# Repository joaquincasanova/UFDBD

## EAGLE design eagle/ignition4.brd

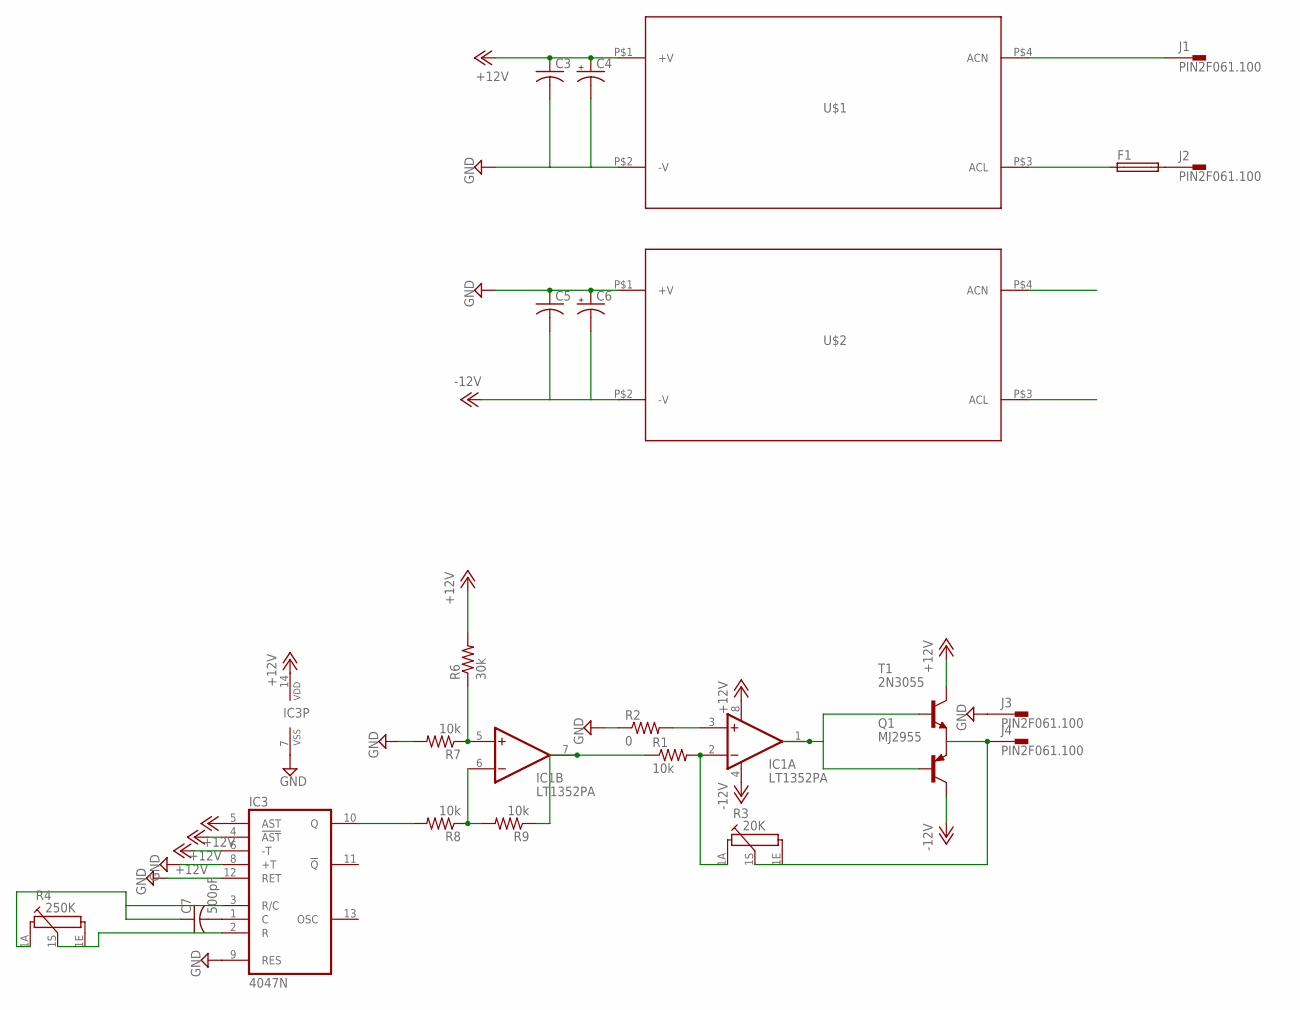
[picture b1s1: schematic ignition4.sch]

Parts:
C3, C5: C-US050-035X075; C050-035X075
C4, C6: CPOL-USE5-5; E5-5
C7: 500pF; C075-042X103
F1: SH25
IC1: LT1352PA; DIL08
IC3: 4047N; DIL14
J1, J2, J3, J4: PIN2F061.100; F061.100
Q1: MJ2955; TO3
R1: 10k; 0207/15
R2: 0; 0207/15
R3: 20K; PC16S
R4: 250K; PC16S
R6: 30k; 0207/12
R7, R8, R9: 10k; 0207/10
T1: 2N3055; TO3
U$1, U$2: IRM-60-12

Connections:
+12V: C3.1, C4.+, IC1.8 (V+), IC3.4 (!AST), IC3.5 (AST), IC3.6 (-T), IC3.14 (VDD), R6.2, T1.C, T1.C/ (C), U$1.P$1 (+V)
-12V: C5.2, C6.-, IC1.4 (V-), Q1.C, Q1.C/ (C), U$2.P$2 (-V)
GND: C3.2, C4.-, C5.1, C6.+, IC3.7 (VSS), IC3.8 (+T), IC3.9 (RES), IC3.12 (RET), J3.A1, J3.A2, R2.1, R7.2, U$1.P$2 (-V), U$2.P$1 (+V)
L: F1.1, U$1.P$3 (ACL), U$2.P$3 (ACL)
N: J1.A1, J1.A2, U$1.P$4 (ACN), U$2.P$4 (ACN)
unnamed: IC1.2 (-IN), R1.2, R3.1A
unnamed: J4.A1, J4.A2, Q1.E, R3.1E, R3.1S, T1.E
unnamed: IC1.7 (OUT), R1.1, R9.1
unnamed: F1.2, J2.A1, J2.A2
unnamed: IC1.1 (OUT), Q1.B, T1.B
unnamed: IC1.3 (+IN), R2.2
unnamed: IC1.5 (+IN), R6.1, R7.1
unnamed: IC1.6 (-IN), R8.1, R9.2
unnamed: IC3.10 (Q), R8.2
unnamed: C7.2, IC3.1 (C)
unnamed: IC3.2 (R), R4.1E, R4.1S
unnamed: C7.1, IC3.3 (R/C), R4.1A

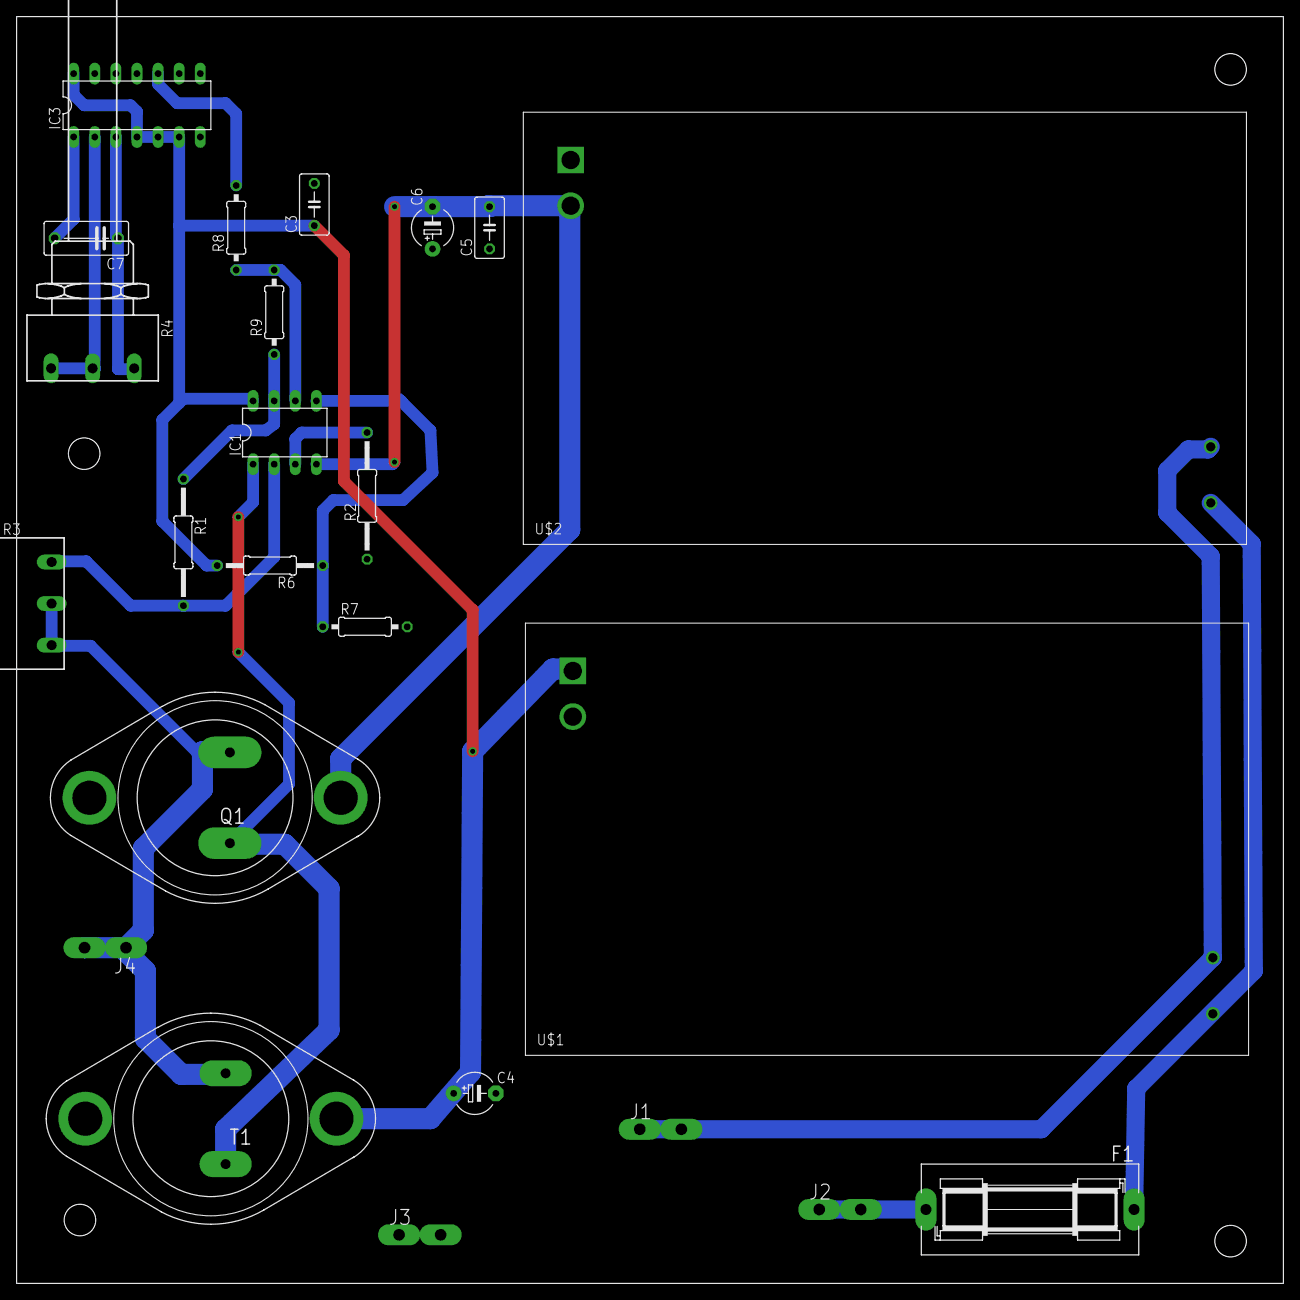
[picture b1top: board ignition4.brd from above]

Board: 2 copper layers, 152.4 x 152.4 mm, 24 parts (0 on the bottom side), 17 nets.

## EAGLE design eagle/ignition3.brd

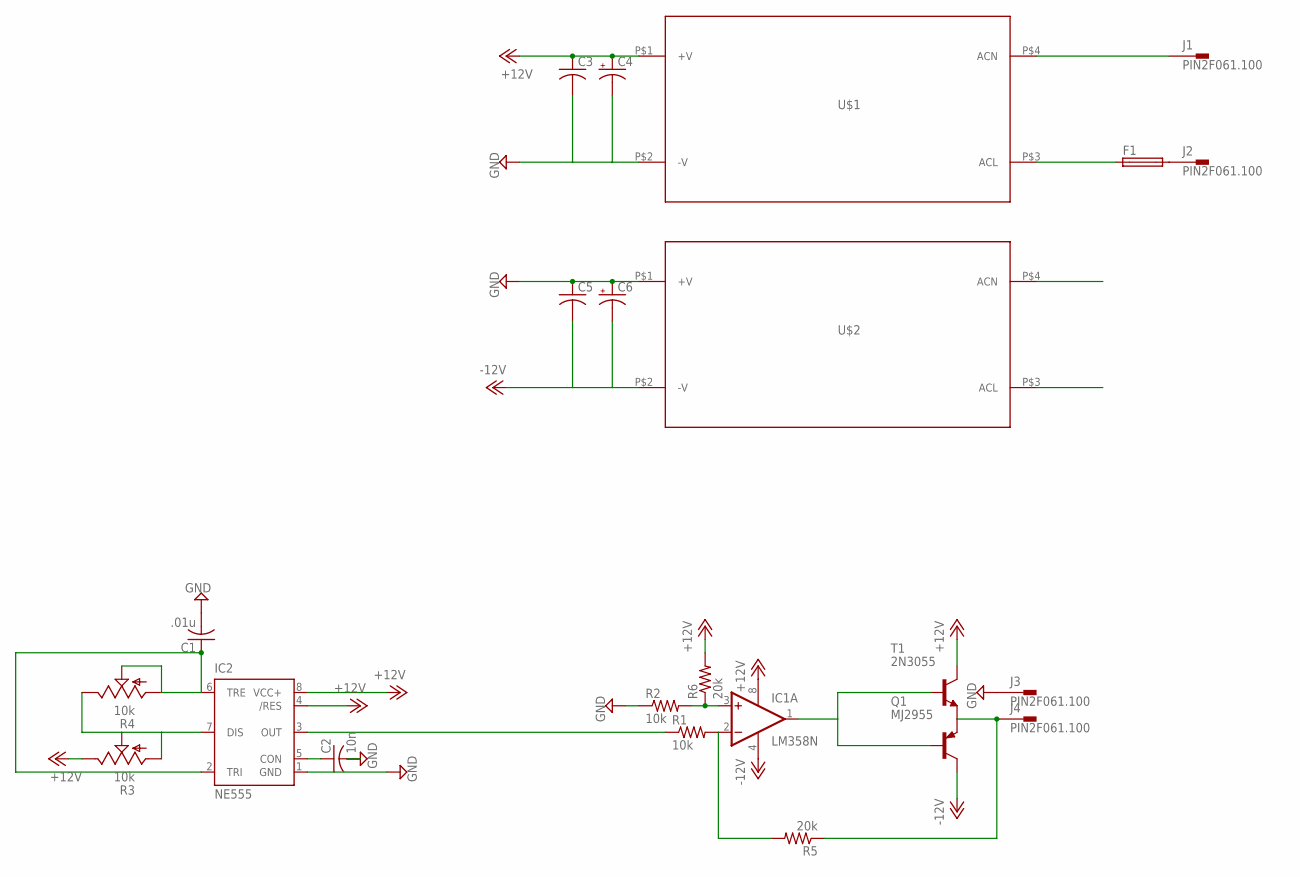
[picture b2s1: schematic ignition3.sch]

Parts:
C1: .01u; C050-035X075
C2: 10n; C075-042X103
C3, C5: C-US050-035X075; C050-035X075
C4, C6: CPOL-USE5-5; E5-5
F1: SH25
IC1: LM358N; DIL08
IC2: NE555; DIL-08
J1, J2, J3, J4: PIN2F061.100; F061.100
Q1: MJ2955; TO3
R1, R2: 10k; 0207/10
R3, R4: 10k; B64Y
R5, R6: 20k; 0207/10
T1: 2N3055; TO3
U$1, U$2: IRM-60-12

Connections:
+12V: C3.1, C4.+, IC1.8 (V+), IC2.4 (/RES), IC2.8 (VCC+), R3.E, R6.2, T1.C, T1.C/ (C), U$1.P$1 (+V)
-12V: C5.2, C6.-, IC1.4 (V-), Q1.C, Q1.C/ (C), U$2.P$2 (-V)
GND: C1.2, C2.2, C3.2, C4.-, C5.1, C6.+, IC2.1 (GND), J3.A1, J3.A2, R2.1, U$1.P$2 (-V), U$2.P$1 (+V)
L: F1.1, U$1.P$3 (ACL), U$2.P$3 (ACL)
N: J1.A1, J1.A2, U$1.P$4 (ACN), U$2.P$4 (ACN)
unnamed: IC1.2 (-IN), R1.2, R5.2
unnamed: C2.1, IC2.5 (CON)
unnamed: J4.A1, J4.A2, Q1.E, R5.1, T1.E
unnamed: F1.2, J2.A1, J2.A2
unnamed: IC1.1 (OUT), Q1.B, T1.B
unnamed: C1.1, IC2.2 (TRI), IC2.6 (TRE), R4.A, R4.S
unnamed: IC2.7 (DIS), R3.A, R3.S, R4.E
unnamed: IC1.3 (+IN), R2.2, R6.1
unnamed: IC2.3 (OUT), R1.1

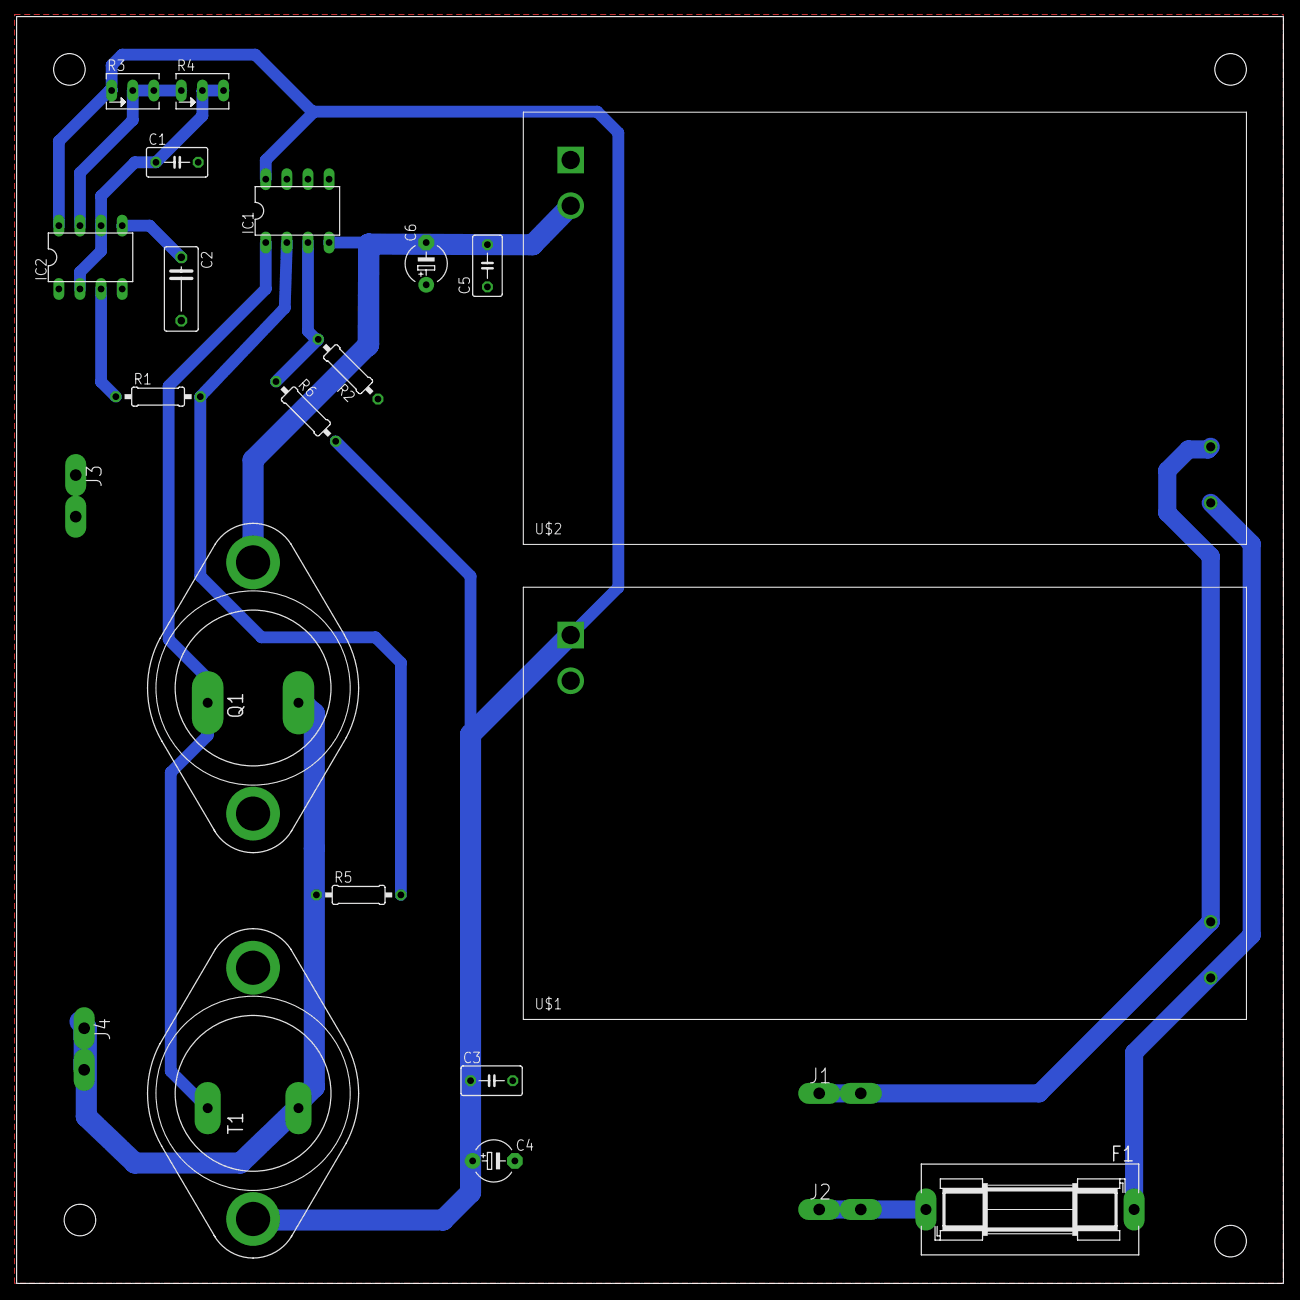
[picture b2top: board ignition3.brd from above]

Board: 2 copper layers, 152.4 x 152.4 mm, 23 parts (0 on the bottom side), 14 nets.

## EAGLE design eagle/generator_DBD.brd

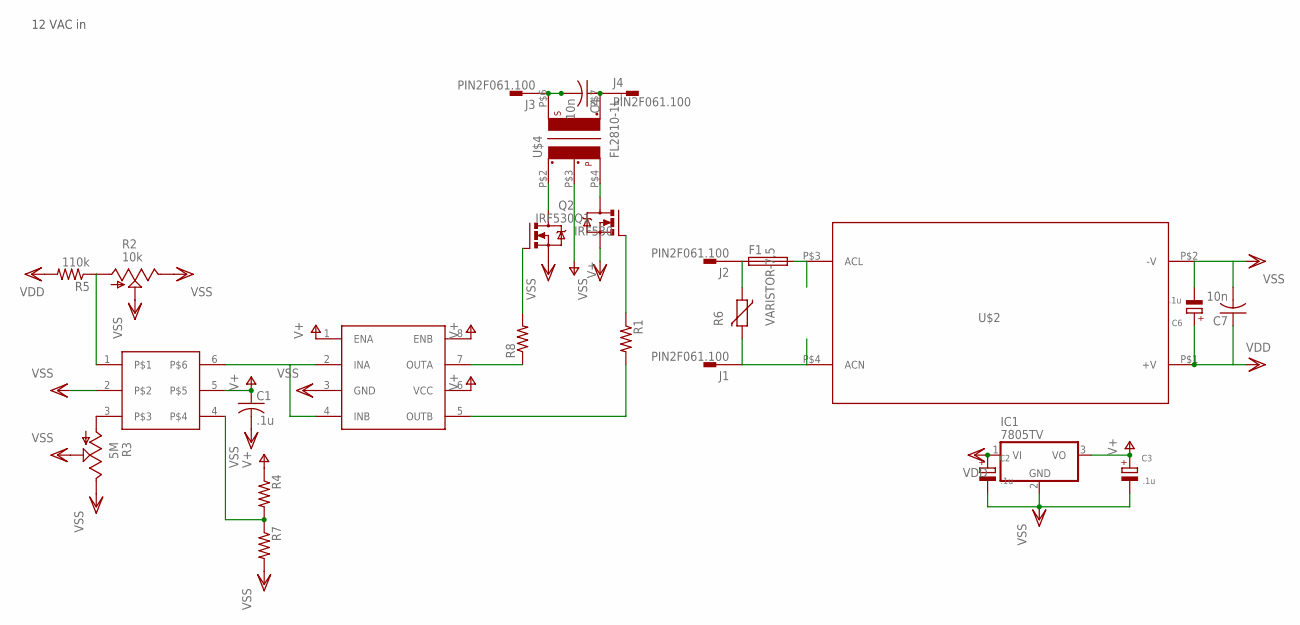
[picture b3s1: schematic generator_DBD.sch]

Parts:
C1: .1u; C075-042X103
C2, C3, C6: .1u; E5-8,5
C4, C7: 10n; C075-042X103
F1: SH25
IC1: 7805TV; TO220V
J1, J2, J3, J4: PIN2F061.100; F061.100
Q1, Q2: IRF530; TO220BV
R1, R4, R7: R-US_0207/10; 0207/10
R2: 10k; PT-SPIN-2
R3: 5M; PT-SPIN-2
R5: 110k; 0207/10
R6: VARISTOR-7,5; R-7,5
R8: R-US_0207/15; 0207/15
U$1: UCC27425; DIL08
U$2: IRM-60-12
U$3: LTC6992SMD; SOT23-6
U$4: FL2810-1L_; 4

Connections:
unnamed: Q2.G, R1.1
unnamed: R3.A, U$3.3
unnamed: R2.A, R5.1, U$3.1
unnamed: F1.1, J2.A1, J2.A2, R6.1
unnamed: U$1.2 (INA), U$1.4 (INB), U$3.6
unnamed: J1.A1, J1.A2, R6.2, U$2.P$4 (ACN)
unnamed: R1.2, U$1.5 (OUTB)
unnamed: F1.2, U$2.P$3 (ACL)
unnamed: R4.2, R7.1, U$3.4
unnamed: R8.1, U$1.7 (OUTA)
unnamed: Q1.G, R8.2
unnamed: Q1.D, U$4.P$2 (1)
unnamed: Q2.D, U$4.P$4 (3)
unnamed: C4.2, J3.A1, J3.A2, U$4.P$6 (6)
unnamed: C4.1, J4.A1, J4.A2, U$4.P$7 (4)
V+: C1.1, C3.+, IC1.3 (VO), R4.1, U$1.1 (ENA), U$1.6 (VCC), U$1.8 (ENB), U$3.5, U$4.P$3 (2)
VDD: C2.+, C6.+, C7.1, IC1.1 (VI), R5.2, U$2.P$1 (+V)
VSS: C1.2, C2.-, C3.-, C6.-, C7.2, IC1.2 (GND), Q1.S, Q2.S, R2.E, R2.S, R3.E, R3.S, R7.2, U$1.3 (GND), U$2.P$2 (-V), U$3.2

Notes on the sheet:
12 VAC in

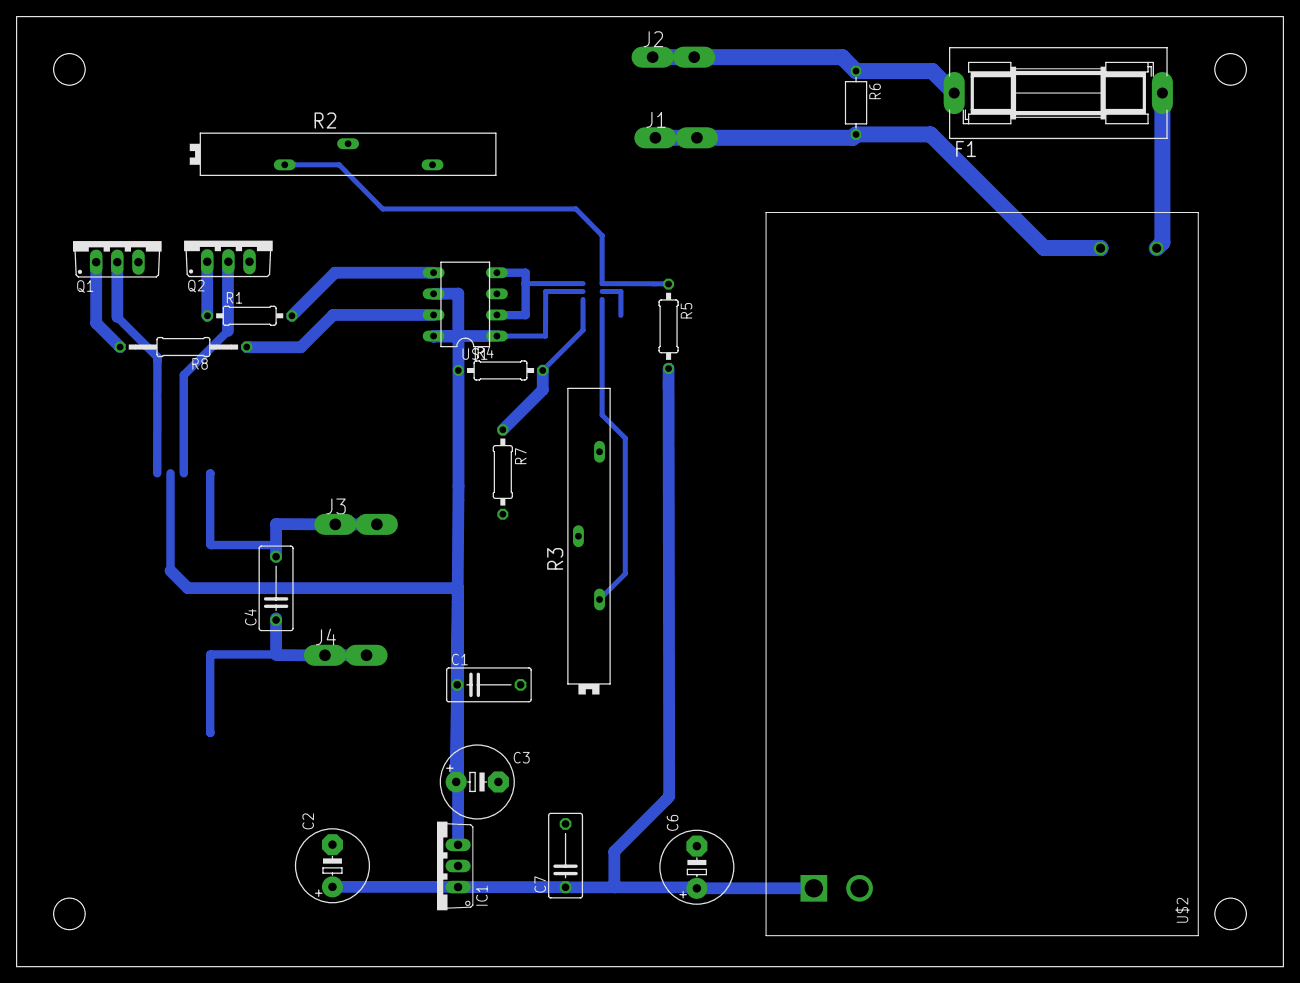
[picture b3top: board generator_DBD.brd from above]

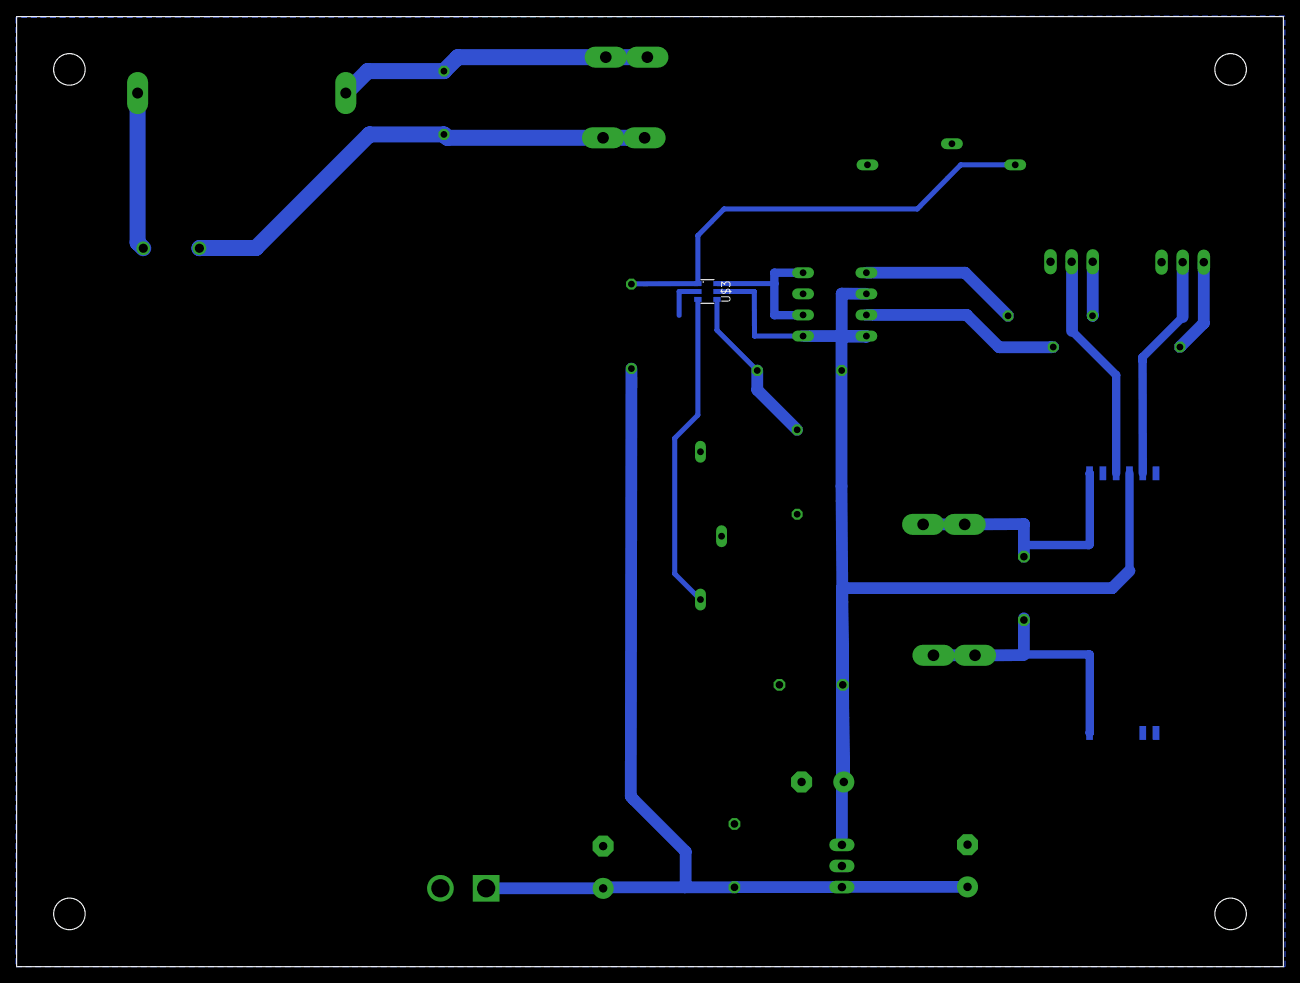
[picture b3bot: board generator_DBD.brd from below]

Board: 2 copper layers, 152.4 x 114.3 mm, 26 parts (2 on the bottom side), 18 nets.

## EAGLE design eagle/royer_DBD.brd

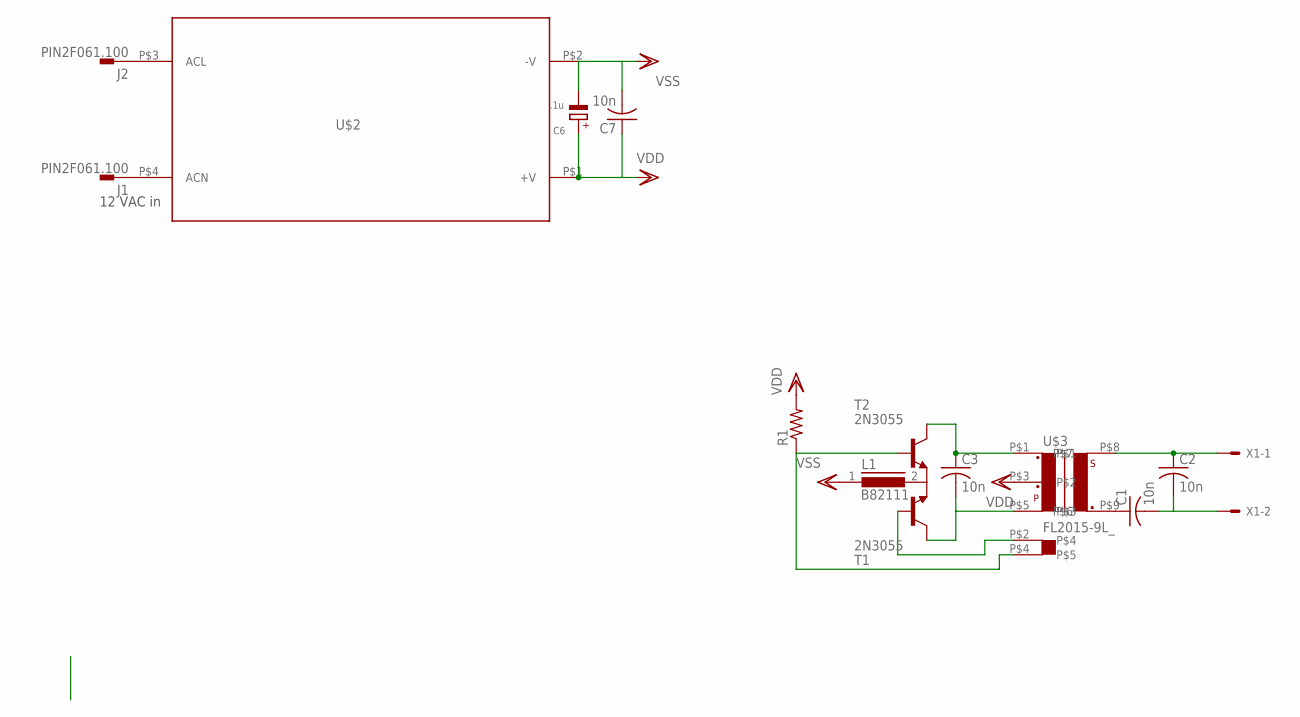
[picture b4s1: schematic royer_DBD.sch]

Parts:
C1, C2, C3, C7: 10n; C075-042X103
C6: .1u; E5-8,5
J1, J2: PIN2F061.100; F061.100
L1: B82111; SUKW1-30
R1: R-US_0207/10; 0207/10
T1, T2: 2N3055; TO3
U$2: IRM-60-12
U$3: FL2015-9L_; 1
X1: KK-156-2

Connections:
unnamed: R1.1, T2.B, U$3.P$4
unnamed: L1.2, T1.E, T2.E
unnamed: C3.1, T2.C, T2.C/ (C), U$3.P$1
unnamed: C3.2, T1.C, T1.C/ (C), U$3.P$5
unnamed: T1.B, U$3.P$2
unnamed: J1.A1, J1.A2, U$2.P$4 (ACN)
unnamed: J2.A1, J2.A2, U$2.P$3 (ACL)
unnamed: C1.1, U$3.P$9
unnamed: C2.1, U$3.P$8, X1.1
unnamed: C1.2, C2.2, X1.2
VDD: C6.+, C7.1, R1.2, U$2.P$1 (+V), U$3.P$3
VSS: C6.-, C7.2, L1.1, U$2.P$2 (-V)

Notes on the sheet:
12 VAC in

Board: 2 copper layers, 14 parts (0 on the bottom side), 12 nets, no tracks yet.

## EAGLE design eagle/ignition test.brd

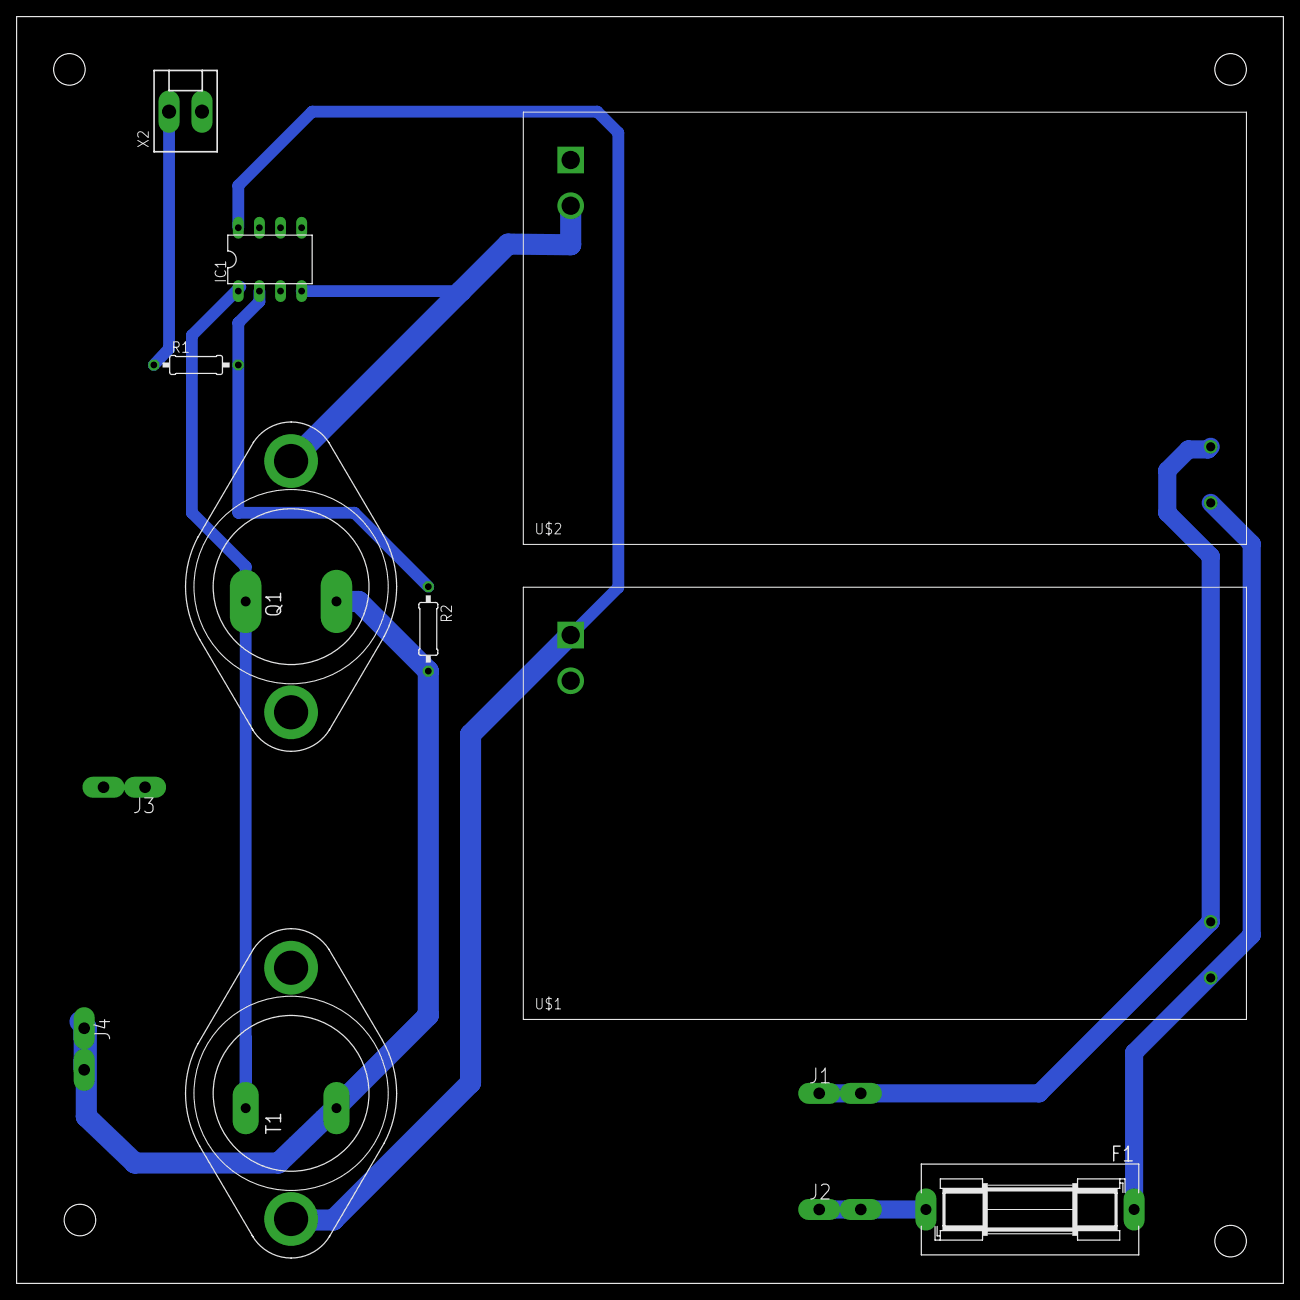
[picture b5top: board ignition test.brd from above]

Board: 2 copper layers, 152.4 x 152.4 mm, 13 parts (0 on the bottom side), 10 nets.

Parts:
F1: SH25
IC1: LM358N; DIL08
J1, J2, J3, J4: PIN2F061.100; F061.100
Q1: MJ2955; TO3
R1, R2: 10k; 0207/10
T1: 2N3055; TO3
U$1, U$2: IRM-60-12
X2: KK-156-2

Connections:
+12V: IC1.8, T1.C, T1.C/, U$1.P$1
-12V: IC1.4, Q1.C, Q1.C/, U$2.P$2
GND: IC1.3, J3.A1, J3.A2, U$1.P$2, U$2.P$1, X2.2
L: F1.1, U$1.P$3, U$2.P$3
N: J1.A1, J1.A2, U$1.P$4, U$2.P$4
unnamed: IC1.2, R1.2, R2.1
unnamed: J4.A1, J4.A2, Q1.E, R2.2, T1.E
unnamed: R1.1, X2.1
unnamed: F1.2, J2.A1, J2.A2
unnamed: IC1.1, Q1.B, T1.B

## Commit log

2015-11-26 :boom::camel: Added .gitattributes & .gitignore files
2015-12-01 papers+boards
2015-12-04 clock on ion board
2015-12-04 gitignore
2015-12-07 BOARDS
2015-12-07 Use cd4047
2015-12-10 fix some things on dbd board
2015-12-11 model
2015-12-14 double it
2015-12-15 asdf
2015-12-17 solidworks
2016-01-22 v2.0
